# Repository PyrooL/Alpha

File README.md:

# Alpha 

A 28-key semi-ortholinear mechanical keyboard designed by PyroL.

###### Photo by /u/Polyzhu.

## History

[First ever post](https://www.reddit.com/r/MechanicalKeyboards/comments/7nz4ge/ic_i_was_challenged_to_reduce_the_gherkin_and/?ref=share&ref_source=link)

[PCB protos arrive](https://www.reddit.com/r/MechanicalKeyboards/comments/887hxn/its_so_cute_c/?ref=share&ref_source=link)

[GB opens](https://www.reddit.com/r/MechanicalKeyboards/comments/8djw3d/gb_alpha_28key_keyboard/?ref=share&ref_source=link)

# Build instructions

## Parts

- [ ] 1x Alpha PCB
- [ ] 28x 1N4148 or equivalent diodes
- [ ] 1x Pro Micro (**NOTE:** USB-C ports are experiencing some clearance issues since it's taller than Micro-B)
- [ ] 1x Case or plate set
- [ ] 5x 10mm M3 standoffs
- [ ] 10x 5mm M3 screws
- [ ] 28x MX, Alps, or Kailh Choc style switches of your choice
- [ ] 1x Micro USB cable

## Tools

- [ ] Soldering station
- [ ] Wire cutter
- [ ] Screwdriver

## Before you start

Orient the PCB correctly before you start the build: the blockers on the side closer to you, and the Pro Micro holes on the left. You should be able to read the "Too. Many. Keys." slogan on the side facing up.

(OPTIONAL): Install a 2u stabilizer.

## Step 1: Diodes

Install and solder the diodes on the bottom of the PCB, with the black line facing the square pad. Cut the excess leads. 

## Step 2: Pro Micro
Insert the short side of the Pro Micro standoffs into the bottom of the PCB, and solder them in from the top.

Mount the two switches that will sit in between the Pro Micro standoffs in the plate and solder them into the PCB at that location. Clip the extruding switch pins after soldering to ensure the Pro Micro will sit flat. 

Mount the Pro Micro on the bottom of the PCB, smooth side facing you. Solder.

[bakingpy has an awesome guide](https://imgur.com/a/M9r3EW9) for an even lower-profile Pro Micro mounting solution that works with Alpha!

**Very important:** after soldering, (regardless of if you mounted normally or bakingpy-style,) use a wire cutter to clip as much of the protruding standoff as possible. With 10mm standoffs this is a snug fit, and it is impossible with the standoffs at full length. Reflow your solder if it climbed up the wire.

## Step 3: Switches

Mount the switches in the plate, and solder them all in. Careful for bent pins!

## Step 4 (OPTIONAL): LED strip

Remove the 3M adhesive strip on the back of your LED strip and place it on the bottom of the PCB. Cut 3 wires of similar length, preferably of different colors. Connect VCC, GND, and Data pins on the strip to their respective pins on the PCB.

v1.1 and onwards has pins labeled and in the same order as they come on the strip!

[**If you are using a v1.0 PCB (one that does not have RGB pins or version number labeled) see here for wiring guide**](photos/instructions/rgb.jpg)

## Step 5: Case and firmware

Assemble the case: for each hole, pass a screw through the top plate, screw in a standoff to finger tightness, then screw in through the bottom plate. Once all screws and standoffs are installed, use a screwdriver to tighten as needed (but not too tight, as acrylic can be brittle!). Flash using QMK (use my firmware, or kbfirmware.com), and enjoy!

Flash steps:

- Download [QMK Toolbox](https://github.com/qmk/qmk_toolbox)
- Ensure that you have an appropriate firmware file.
  - For Vial, you can download one off of [keyboard.gay](https://keyboard.gay)
- Open QMK Toolbox. Plug your PCB in, and press the SKQG reset button (or short the appropriate headers). You should see the device connect for ~10 seconds, then disconnect.
- Within QMK Toolbox, choose your appropriate firmware file, then check the "Auto-Flash" button.
- Reset your board again. The firmware should be automatically flashed onto the board.

Don't forget to send me a pic of your build at @PyroL#7672 on Discord or /u/pyrocrastinator! I'd love to see what you guys do with these! 

# Changelog
* v1.1 3/2/19

Added SKQG reset button pads (no need to manually short reset!) and fixed RGB pin order to match common SK6812/WS2812 pinout, and added silkscreen labels to RGB pins.

* v1.2 4/27/19

Diodes now are combo through-hole and SMD compatible! Breakout pins for artisan column ("tmo28") added on both sides. Routing cleaned up etc. 

* v2.0 7/21/19

Choc footprints added! Also support for first version of "TMO28", an artisan column that's still being worked on. 

* v2.1 9/1/19

Fixed disconnected D4, see [here](https://www.instagram.com/p/B15MHgMnYID/?igshid=1266ym89zlw4w) or contact me for fix if you are affected. Only affects v2.0.

* v2.2 7/24/20

Removed TMO28 breakout pins for cleaner look. Version with breakouts still available in `breakoutholes` branch.

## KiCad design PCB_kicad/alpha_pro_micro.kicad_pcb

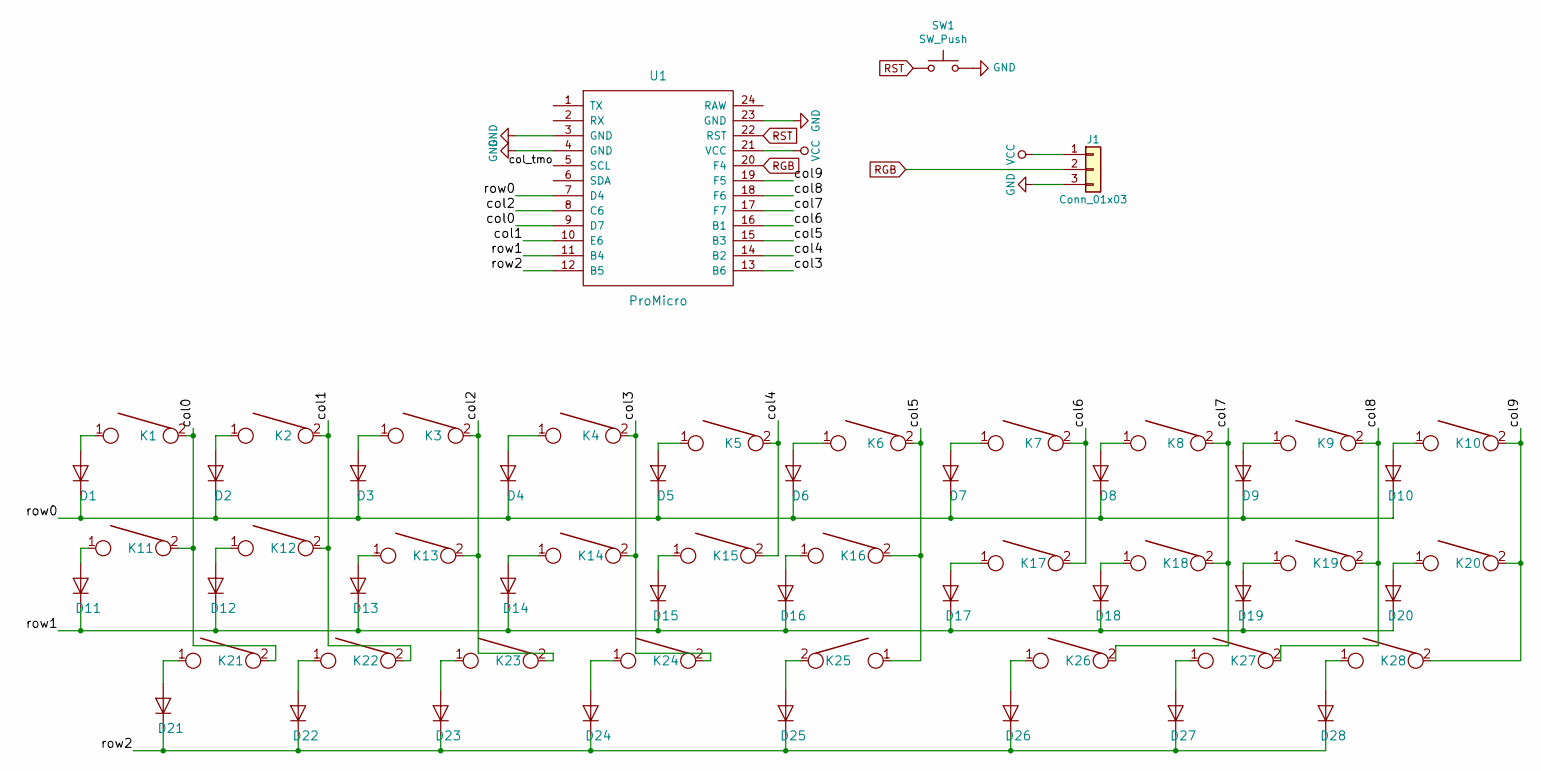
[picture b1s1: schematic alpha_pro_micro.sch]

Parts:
D1, D2, D3, D4, D5, D6, D7, D8, D9, D10, D11, D12, D13, D14, D15, D16, D17, D18, D19, D20, D21, D22, D23, D24, D25, D26, D27, D28: D; ComboDiode
J1: Conn_01x03; Pin_Header_Straight_1x03_Pitch2.54mm
K1, K2, K3, K4, K5, K6, K7, K8, K9, K10, K11, K12, K13, K14, K15, K16, K17, K18, K19, K20, K21, K22, K23, K24, K26, K27, K28: KEYSW; MX-Alps-Choc-1U-NoLED
K25: KEYSW; MX-Alps-Choc-2U-StabFlip
SW1: SW_Push; SKQG-1155865
U1: ProMicro

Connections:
/col0: K1.2, K11.2, K21.2, U1.9 (D7)
/col1: K2.2, K12.2, K22.2, U1.10 (E6)
/col2: K3.2, K13.2, K23.2, U1.8 (C6)
/col3: K4.2, K14.2, K24.2, U1.13 (B6)
/col4: K5.2, K15.2, U1.14 (B2)
/col5: K6.2, K16.2, K25.1, U1.15 (B3)
/col6: K7.2, K17.2, U1.16 (B1)
/col7: K8.2, K18.2, K26.2, U1.17 (F7)
/col8: K9.2, K19.2, K27.2, U1.18 (F6)
/col9: K10.2, K20.2, K28.2, U1.19 (F5)
/col_tmo: U1.5 (SCL)
/row0: D1.1 (K), D2.1 (K), D3.1 (K), D4.1 (K), D5.1 (K), D6.1 (K), D7.1 (K), D8.1 (K), D9.1 (K), D10.1 (K), U1.7 (D4)
/row1: D11.1 (K), D12.1 (K), D13.1 (K), D14.1 (K), D15.1 (K), D16.1 (K), D17.1 (K), D18.1 (K), D19.1 (K), D20.1 (K), U1.11 (B4)
/row2: D21.1 (K), D22.1 (K), D23.1 (K), D24.1 (K), D25.1 (K), D26.1 (K), D27.1 (K), D28.1 (K), U1.12 (B5)
GND: J1.3, SW1.2, U1.3 (GND), U1.4 (GND), U1.23 (GND)
unnamed: D1.2 (A), K1.1
unnamed: D2.2 (A), K2.1
unnamed: D3.2 (A), K3.1
unnamed: D4.2 (A), K4.1
unnamed: D5.2 (A), K5.1
unnamed: D6.2 (A), K6.1
unnamed: D7.2 (A), K7.1
unnamed: D8.2 (A), K8.1
unnamed: D9.2 (A), K9.1
unnamed: D10.2 (A), K10.1
unnamed: D11.2 (A), K11.1
unnamed: D12.2 (A), K12.1
unnamed: D13.2 (A), K13.1
unnamed: D14.2 (A), K14.1
unnamed: D15.2 (A), K15.1
unnamed: D16.2 (A), K16.1
unnamed: D17.2 (A), K17.1
unnamed: D18.2 (A), K18.1
unnamed: D19.2 (A), K19.1
unnamed: D20.2 (A), K20.1
unnamed: D21.2 (A), K21.1
unnamed: D22.2 (A), K22.1
unnamed: D23.2 (A), K23.1
unnamed: D24.2 (A), K24.1
unnamed: D25.2 (A), K25.2
unnamed: D26.2 (A), K26.1
unnamed: D27.2 (A), K27.1
unnamed: D28.2 (A), K28.1
RGB: J1.2, U1.20 (F4)
RST: SW1.1, U1.22 (RST)
VCC: J1.1, U1.21 (VCC)

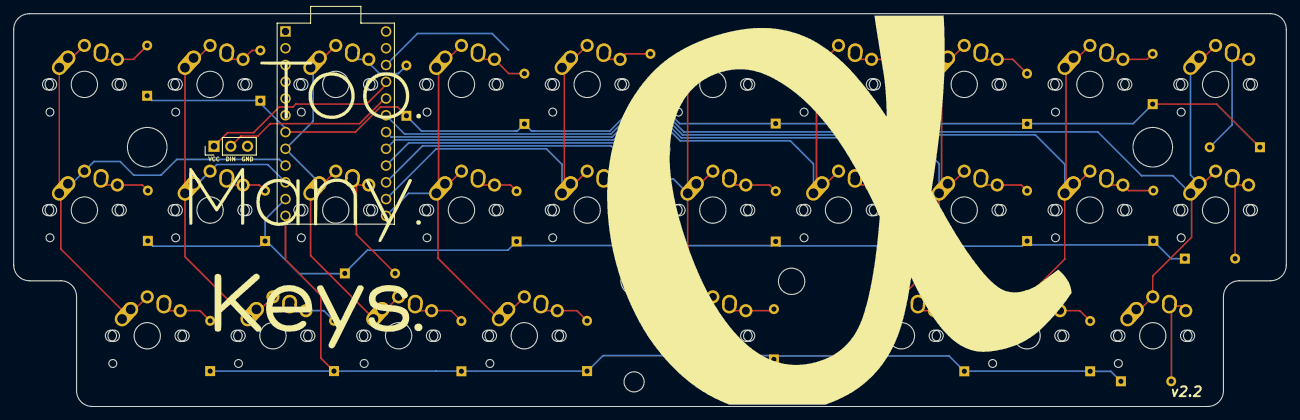
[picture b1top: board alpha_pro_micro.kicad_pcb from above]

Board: 2 copper layers, 192.9 x 59.5 mm, 60 parts (1 on the bottom side), 45 nets.

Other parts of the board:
HC1: MountingHole_6mm

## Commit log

2018-04-12 Add files via upload
    Designs for top and bottom plate.
2018-06-16 designs finalizing b4 gb
2018-08-19 test
2018-08-19 test 2 electric boogaloo
2018-08-19 readme unbropk
2018-08-19 format
2018-08-19 im picky lo
2018-08-19 not good enough
2018-08-19 added gerbers \o/
2018-08-19 plate
2018-08-19 parts
2018-09-05 plate readme
2018-09-05 photo disclaimer
2018-09-06 bakingpy pro micro mount
2018-09-06 tips n tricks
2018-09-09 photo organization and keymap test
2018-09-10 Keymap explanation
2018-09-10 RGB control clarification
2018-09-18 MIT License
2018-10-02 im not very intelligent
2018-10-15 timeline
2018-12-07 photo
2019-02-07 USB-C warning
2019-03-03 Alpha v1.1 + design files
2019-03-27 Set theme jekyll-theme-minimal
2019-03-27 github pages repo
2019-03-27 docs folder for github pages
2019-03-27 how does jekyll work
2019-03-27 figuring things out
2019-03-27 "oof"
2019-03-28 Squash commits
2019-03-28 28/03
2019-03-28 44 years ago we put a man on the moon, yet we still can’t vertically centre things in CSS.
2019-03-28 help i'm stuck in a dark room writing css
2019-03-28 "less bad"
2019-03-28 less bad
2019-03-28 Touching up final aesthetic
2019-03-29 "yes"
2019-04-27 PCB v1.2!
2019-04-27 v1.2 README + Gerbers
2019-04-27 changelog
2019-04-29 pyrool.github.io/Alpha
2019-06-06 gerber update
2019-07-21 Alpha v2.0 released!
2019-07-29 updated gerbers
2019-07-30 quick choc support stuff
2019-08-25 working on the website
2019-08-25 small edits docs
2019-09-02 v2.1 released: fixed disconnected D4
2019-09-02 v2.1 release notes
2020-03-28 removed tmo28 breakouts
2020-05-04 Clarified plate readme
2020-07-25 v2.2
2020-07-25 tiny fix
2020-10-10 removed .DS_Store lol
2022-08-26 compiled v2.2 gerbers
2023-10-21 V2.2 gerbers, forgot to push ages ago hehe
2024-04-08 Update README.md
    Adding flashing instructions for the next person that's as clueless as me.
